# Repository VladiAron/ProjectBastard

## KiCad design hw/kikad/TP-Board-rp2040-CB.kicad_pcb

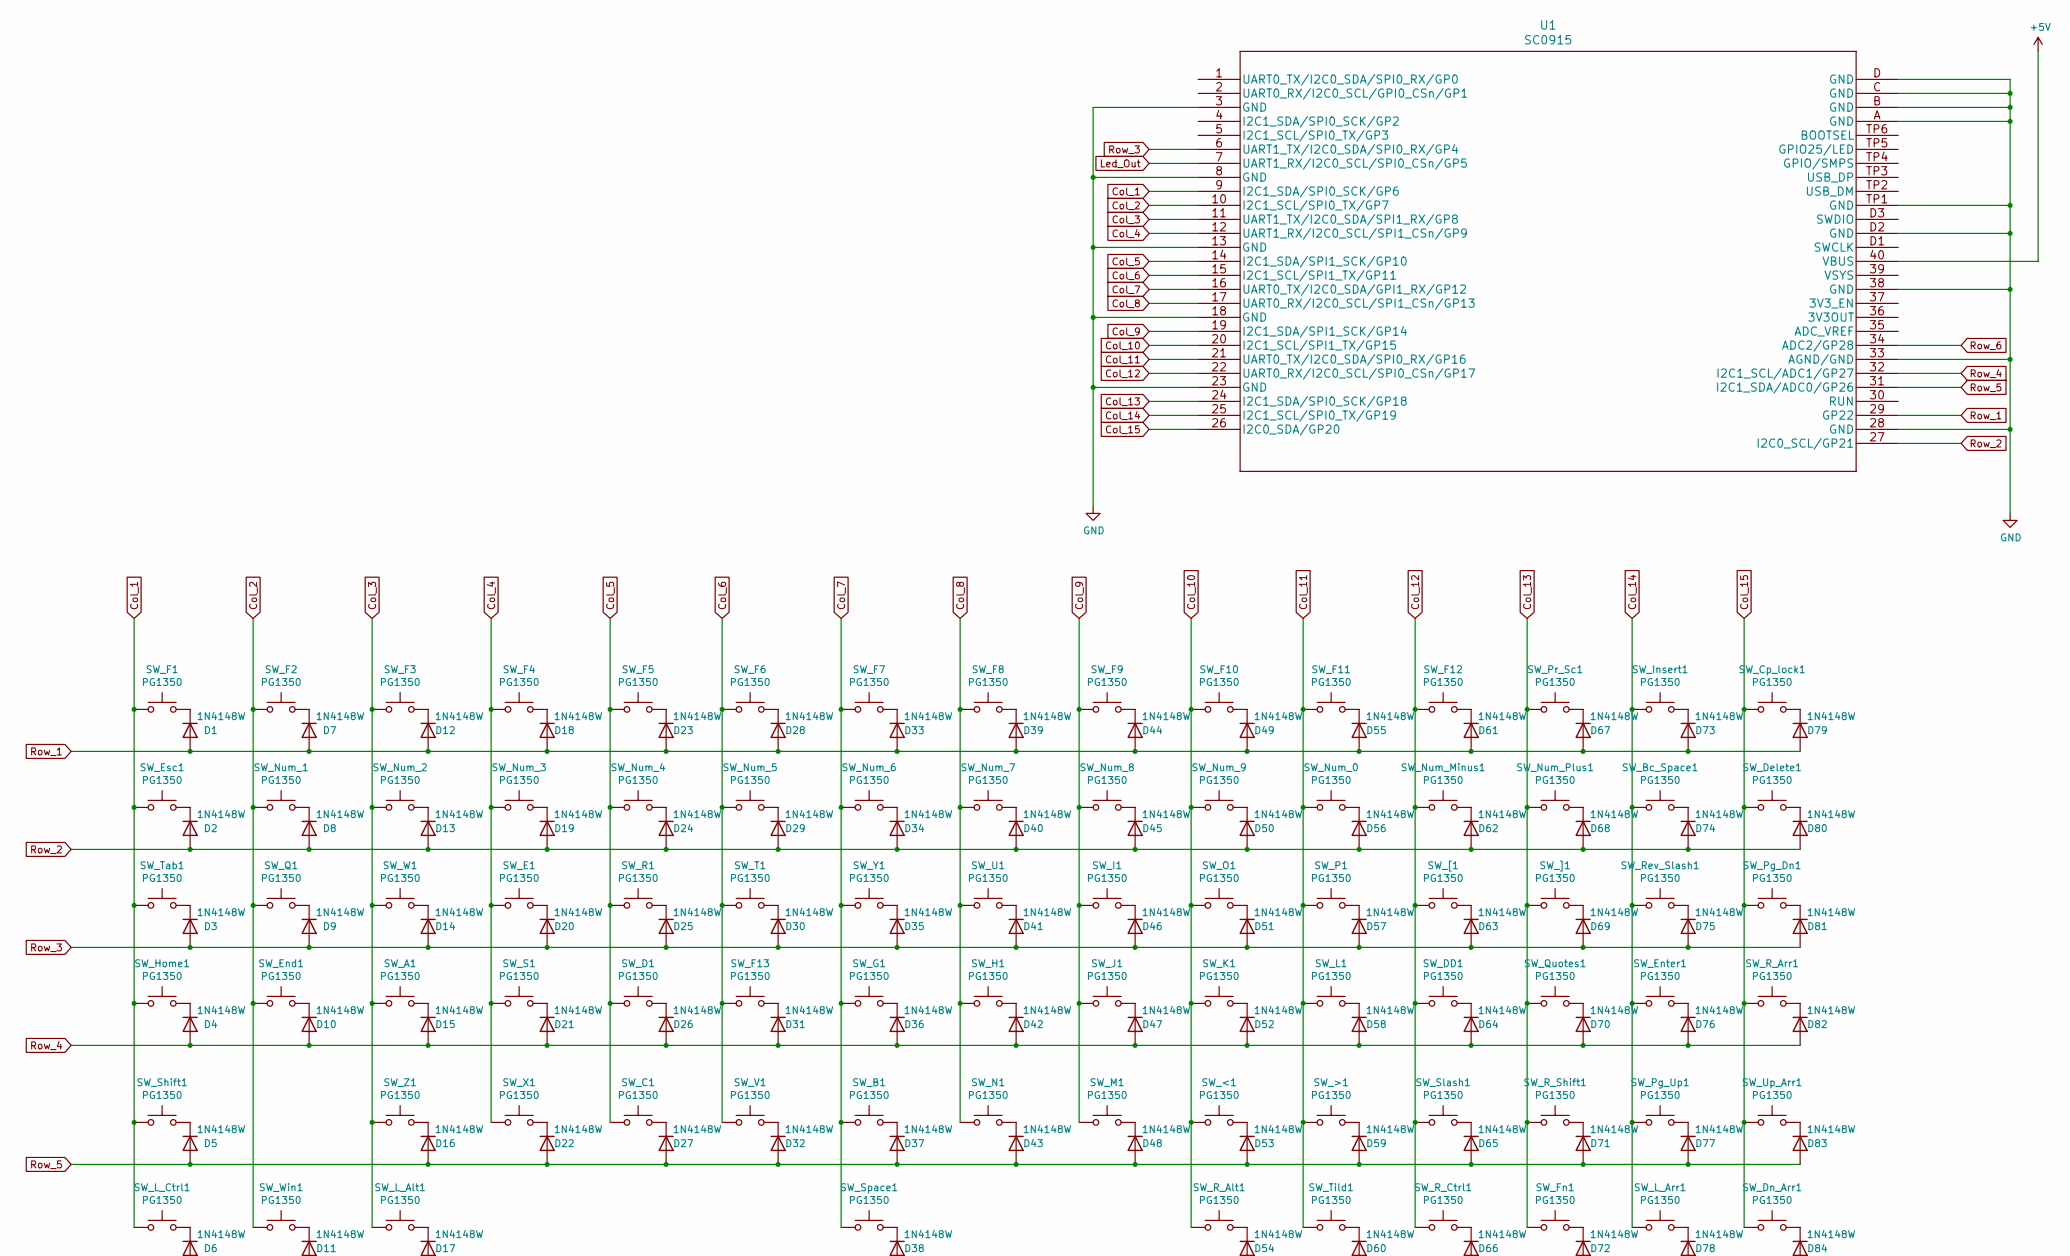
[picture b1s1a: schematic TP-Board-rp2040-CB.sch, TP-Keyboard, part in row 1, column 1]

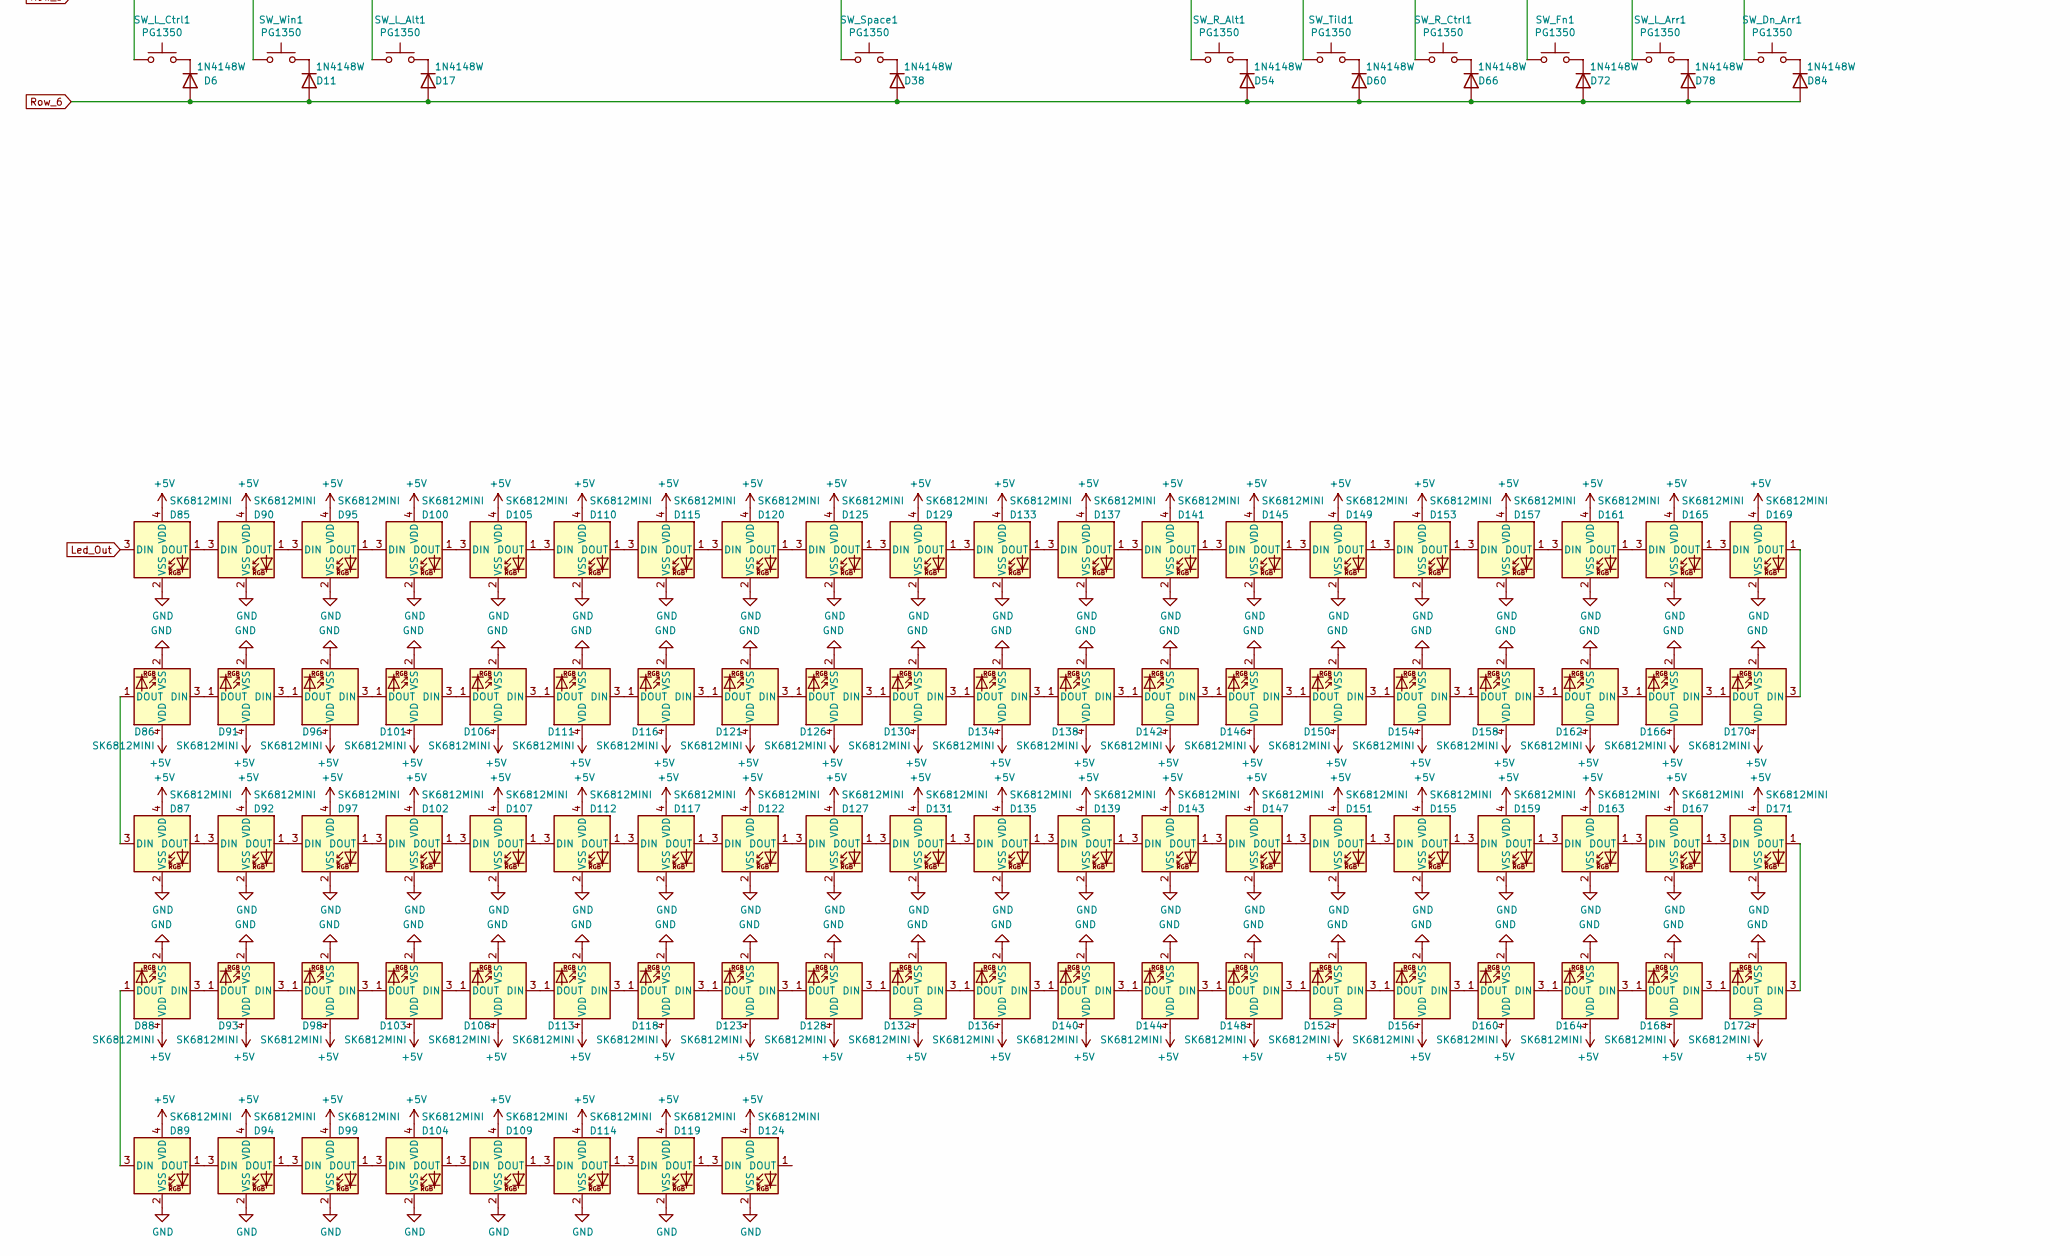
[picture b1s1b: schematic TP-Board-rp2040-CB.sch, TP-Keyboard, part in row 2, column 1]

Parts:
D1, D2, D3, D4, D5, D6, D7, D8, D9, D10, D11, D12, D13, D14, D15, D16, D17, D18, D19, D20, D21, D22, D23, D24, D25, D26, D27, D28, D29, D30, D31, D32, D33, D34, D35, D36, D37, D38, D39, D40, D41, D42, D43, D44, D45, D46, D47, D48, D49, D50, D51, D52, D53, D54, D55, D56, D57, D58, D59, D60, D61, D62, D63, D64, D65, D66, D67, D68, D69, D70, D71, D72, D73, D74, D75, D76, D77, D78, D79, D80, D81, D82, D83, D84: 1N4148W; D_SOD-123
D85, D86, D87, D88, D89, D90, D91, D92, D93, D94, D95, D96, D97, D98, D99, D100, D101, D102, D103, D104, D105, D106, D107, D108, D109, D110, D111, D112, D113, D114, D115, D116, D117, D118, D119, D120, D121, D122, D123, D124, D125, D126, D127, D128, D129, D130, D131, D132, D133, D134, D135, D136, D137, D138, D139, D140, D141, D142, D143, D144, D145, D146, D147, D148, D149, D150, D151, D152, D153, D154, D155, D156, D157, D158, D159, D160, D161, D162, D163, D164, D165, D166, D167, D168, D169, D170, D171, D172: SK6812MINI; LED_SK6812MINI_PLCC4_3.5x3.5mm_P1.75mm
SW_<1: PG1350; SW_PG1350
SW_>1: PG1350; SW_PG1350
SW_A1: PG1350; SW_PG1350
SW_B1: PG1350; SW_PG1350
SW_Bc_Space1: PG1350; SW_PG1350
SW_C1: PG1350; SW_PG1350
SW_Cp_lock1: PG1350; SW_PG1350
SW_D1: PG1350; SW_PG1350
SW_DD1: PG1350; SW_PG1350
SW_Delete1: PG1350; SW_PG1350
SW_Dn_Arr1: PG1350; SW_PG1350
SW_E1: PG1350; SW_PG1350
SW_End1: PG1350; SW_PG1350
SW_Enter1: PG1350; SW_PG1350
SW_Esc1: PG1350; SW_PG1350
SW_F1, SW_F2, SW_F3, SW_F4, SW_F5, SW_F6, SW_F7, SW_F8, SW_F9, SW_F10, SW_F11, SW_F12, SW_F13: PG1350; SW_PG1350
SW_Fn1: PG1350; SW_PG1350
SW_G1: PG1350; SW_PG1350
SW_H1: PG1350; SW_PG1350
SW_Home1: PG1350; SW_PG1350
SW_I1: PG1350; SW_PG1350
SW_Insert1: PG1350; SW_PG1350
SW_J1: PG1350; SW_PG1350
SW_K1: PG1350; SW_PG1350
SW_L1: PG1350; SW_PG1350
SW_L_Alt1: PG1350; SW_PG1350
SW_L_Arr1: PG1350; SW_PG1350
SW_L_Ctrl1: PG1350; SW_PG1350
SW_M1: PG1350; SW_PG1350
SW_N1: PG1350; SW_PG1350
SW_Num_0, SW_Num_1, SW_Num_2, SW_Num_3, SW_Num_4, SW_Num_5, SW_Num_6, SW_Num_7, SW_Num_8, SW_Num_9: PG1350; SW_PG1350
SW_Num_Minus1: PG1350; SW_PG1350
SW_Num_Plus1: PG1350; SW_PG1350
SW_O1: PG1350; SW_PG1350
SW_P1: PG1350; SW_PG1350
SW_Pg_Dn1: PG1350; SW_PG1350
SW_Pg_Up1: PG1350; SW_PG1350
SW_Pr_Sc1: PG1350; SW_PG1350
SW_Q1: PG1350; SW_PG1350
SW_Quotes1: PG1350; SW_PG1350
SW_R1: PG1350; SW_PG1350
SW_R_Alt1: PG1350; SW_PG1350
SW_R_Arr1: PG1350; SW_PG1350
SW_R_Ctrl1: PG1350; SW_PG1350
SW_R_Shift1: PG1350; SW_PG1350
SW_Rev_Slash1: PG1350; SW_PG1350
SW_S1: PG1350; SW_PG1350
SW_Shift1: PG1350; SW_PG1350
SW_Slash1: PG1350; SW_PG1350
SW_Space1: PG1350; SW_PG1350
SW_T1: PG1350; SW_PG1350
SW_Tab1: PG1350; SW_PG1350
SW_Tild1: PG1350; SW_PG1350
SW_U1: PG1350; SW_PG1350
SW_Up_Arr1: PG1350; SW_PG1350
SW_V1: PG1350; SW_PG1350
SW_W1: PG1350; SW_PG1350
SW_Win1: PG1350; SW_PG1350
SW_X1: PG1350; SW_PG1350
SW_Y1: PG1350; SW_PG1350
SW_Z1: PG1350; SW_PG1350
SW_[1: PG1350; SW_PG1350
SW_]1: PG1350; SW_PG1350
U1: SC0915; RPi_Pico_SMD_TH

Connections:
+5V: D85.4 (VDD), D86.4 (VDD), D87.4 (VDD), D88.4 (VDD), D89.4 (VDD), D90.4 (VDD), D91.4 (VDD), D92.4 (VDD), D93.4 (VDD), D94.4 (VDD), D95.4 (VDD), D96.4 (VDD), D97.4 (VDD), D98.4 (VDD), D99.4 (VDD), D100.4 (VDD), D101.4 (VDD), D102.4 (VDD), D103.4 (VDD), D104.4 (VDD), D105.4 (VDD), D106.4 (VDD), D107.4 (VDD), D108.4 (VDD), D109.4 (VDD), D110.4 (VDD), D111.4 (VDD), D112.4 (VDD), D113.4 (VDD), D114.4 (VDD), D115.4 (VDD), D116.4 (VDD), D117.4 (VDD), D118.4 (VDD), D119.4 (VDD), D120.4 (VDD), D121.4 (VDD), D122.4 (VDD), D123.4 (VDD), D124.4 (VDD), D125.4 (VDD), D126.4 (VDD), D127.4 (VDD), D128.4 (VDD), D129.4 (VDD), D130.4 (VDD), D131.4 (VDD), D132.4 (VDD), D133.4 (VDD), D134.4 (VDD), D135.4 (VDD), D136.4 (VDD), D137.4 (VDD), D138.4 (VDD), D139.4 (VDD), D140.4 (VDD), D141.4 (VDD), D142.4 (VDD), D143.4 (VDD), D144.4 (VDD), D145.4 (VDD), D146.4 (VDD), D147.4 (VDD), D148.4 (VDD), D149.4 (VDD), D150.4 (VDD), D151.4 (VDD), D152.4 (VDD), D153.4 (VDD), D154.4 (VDD), D155.4 (VDD), D156.4 (VDD), D157.4 (VDD), D158.4 (VDD), D159.4 (VDD), D160.4 (VDD), D161.4 (VDD), D162.4 (VDD), D163.4 (VDD), D164.4 (VDD), D165.4 (VDD), D166.4 (VDD), D167.4 (VDD), D168.4 (VDD), D169.4 (VDD), D170.4 (VDD), D171.4 (VDD), D172.4 (VDD), U1.40 (VBUS)
Col_1: SW_Esc1.1, SW_F1.1, SW_Home1.1, SW_L_Ctrl1.1, SW_Shift1.1, SW_Tab1.1, U1.9 (I2C1_SDA/SPI0_SCK/GP6)
Col_2: SW_End1.1, SW_F2.1, SW_Num_1.1, SW_Q1.1, SW_Win1.1, U1.10 (I2C1_SCL/SPI0_TX/GP7)
Col_3: SW_A1.1, SW_F3.1, SW_L_Alt1.1, SW_Num_2.1, SW_W1.1, SW_Z1.1, U1.11 (UART1_TX/I2C0_SDA/SPI1_RX/GP8)
Col_4: SW_E1.1, SW_F4.1, SW_Num_3.1, SW_S1.1, SW_X1.1, U1.12 (UART1_RX/I2C0_SCL/SPI1_CSn/GP9)
Col_5: SW_C1.1, SW_D1.1, SW_F5.1, SW_Num_4.1, SW_R1.1, U1.14 (I2C1_SDA/SPI1_SCK/GP10)
Col_6: SW_F6.1, SW_F13.1, SW_Num_5.1, SW_T1.1, SW_V1.1, U1.15 (I2C1_SCL/SPI1_TX/GP11)
Col_7: SW_B1.1, SW_F7.1, SW_G1.1, SW_Num_6.1, SW_Space1.1, SW_Y1.1, U1.16 (UART0_TX/I2C0_SDA/GPI1_RX/GP12)
Col_8: SW_F8.1, SW_H1.1, SW_N1.1, SW_Num_7.1, SW_U1.1, U1.17 (UART0_RX/I2C0_SCL/SPI1_CSn/GP13)
Col_9: SW_F9.1, SW_I1.1, SW_J1.1, SW_M1.1, SW_Num_8.1, U1.19 (I2C1_SDA/SPI1_SCK/GP14)
Col_10: SW_<1.1, SW_F10.1, SW_K1.1, SW_Num_9.1, SW_O1.1, SW_R_Alt1.1, U1.20 (I2C1_SCL/SPI1_TX/GP15)
Col_11: SW_>1.1, SW_F11.1, SW_L1.1, SW_Num_0.1, SW_P1.1, SW_Tild1.1, U1.21 (UART0_TX/I2C0_SDA/SPI0_RX/GP16)
Col_12: SW_DD1.1, SW_F12.1, SW_Num_Minus1.1, SW_R_Ctrl1.1, SW_Slash1.1, SW_[1.1, U1.22 (UART0_RX/I2C0_SCL/SPI0_CSn/GP17)
Col_13: SW_Fn1.1, SW_Num_Plus1.1, SW_Pr_Sc1.1, SW_Quotes1.1, SW_R_Shift1.1, SW_]1.1, U1.24 (I2C1_SDA/SPI0_SCK/GP18)
Col_14: SW_Bc_Space1.1, SW_Enter1.1, SW_Insert1.1, SW_L_Arr1.1, SW_Pg_Up1.1, SW_Rev_Slash1.1, U1.25 (I2C1_SCL/SPI0_TX/GP19)
Col_15: SW_Cp_lock1.1, SW_Delete1.1, SW_Dn_Arr1.1, SW_Pg_Dn1.1, SW_R_Arr1.1, SW_Up_Arr1.1, U1.26 (I2C0_SDA/GP20)
GND: D85.2 (VSS), D86.2 (VSS), D87.2 (VSS), D88.2 (VSS), D89.2 (VSS), D90.2 (VSS), D91.2 (VSS), D92.2 (VSS), D93.2 (VSS), D94.2 (VSS), D95.2 (VSS), D96.2 (VSS), D97.2 (VSS), D98.2 (VSS), D99.2 (VSS), D100.2 (VSS), D101.2 (VSS), D102.2 (VSS), D103.2 (VSS), D104.2 (VSS), D105.2 (VSS), D106.2 (VSS), D107.2 (VSS), D108.2 (VSS), D109.2 (VSS), D110.2 (VSS), D111.2 (VSS), D112.2 (VSS), D113.2 (VSS), D114.2 (VSS), D115.2 (VSS), D116.2 (VSS), D117.2 (VSS), D118.2 (VSS), D119.2 (VSS), D120.2 (VSS), D121.2 (VSS), D122.2 (VSS), D123.2 (VSS), D124.2 (VSS), D125.2 (VSS), D126.2 (VSS), D127.2 (VSS), D128.2 (VSS), D129.2 (VSS), D130.2 (VSS), D131.2 (VSS), D132.2 (VSS), D133.2 (VSS), D134.2 (VSS), D135.2 (VSS), D136.2 (VSS), D137.2 (VSS), D138.2 (VSS), D139.2 (VSS), D140.2 (VSS), D141.2 (VSS), D142.2 (VSS), D143.2 (VSS), D144.2 (VSS), D145.2 (VSS), D146.2 (VSS), D147.2 (VSS), D148.2 (VSS), D149.2 (VSS), D150.2 (VSS), D151.2 (VSS), D152.2 (VSS), D153.2 (VSS), D154.2 (VSS), D155.2 (VSS), D156.2 (VSS), D157.2 (VSS), D158.2 (VSS), D159.2 (VSS), D160.2 (VSS), D161.2 (VSS), D162.2 (VSS), D163.2 (VSS), D164.2 (VSS), D165.2 (VSS), D166.2 (VSS), D167.2 (VSS), D168.2 (VSS), D169.2 (VSS), D170.2 (VSS), D171.2 (VSS), D172.2 (VSS), U1.3 (GND), U1.8 (GND), U1.13 (GND), U1.18 (GND), U1.23 (GND), U1.28 (GND), U1.33 (AGND/GND), U1.38 (GND), U1.A (GND), U1.B (GND), U1.C (GND), U1.D (GND), U1.D2 (GND), U1.TP1 (GND)
Led_Out: D85.3 (DIN), U1.7 (UART1_RX/I2C0_SCL/SPI0_CSn/GP5)
unnamed: D1.1 (K), SW_F1.2
unnamed: D2.1 (K), SW_Esc1.2
unnamed: D3.1 (K), SW_Tab1.2
unnamed: D4.1 (K), SW_Home1.2
unnamed: D5.1 (K), SW_Shift1.2
unnamed: D6.1 (K), SW_L_Ctrl1.2
unnamed: D7.1 (K), SW_F2.2
unnamed: D8.1 (K), SW_Num_1.2
unnamed: D9.1 (K), SW_Q1.2
unnamed: D10.1 (K), SW_End1.2
unnamed: D11.1 (K), SW_Win1.2
unnamed: D12.1 (K), SW_F3.2
unnamed: D13.1 (K), SW_Num_2.2
unnamed: D14.1 (K), SW_W1.2
unnamed: D15.1 (K), SW_A1.2
unnamed: D16.1 (K), SW_Z1.2
unnamed: D17.1 (K), SW_L_Alt1.2
unnamed: D18.1 (K), SW_F4.2
unnamed: D19.1 (K), SW_Num_3.2
unnamed: D20.1 (K), SW_E1.2
unnamed: D21.1 (K), SW_S1.2
unnamed: D22.1 (K), SW_X1.2
unnamed: D23.1 (K), SW_F5.2
unnamed: D24.1 (K), SW_Num_4.2
unnamed: D25.1 (K), SW_R1.2
unnamed: D26.1 (K), SW_D1.2
unnamed: D27.1 (K), SW_C1.2
unnamed: D28.1 (K), SW_F6.2
unnamed: D29.1 (K), SW_Num_5.2
unnamed: D30.1 (K), SW_T1.2
unnamed: D31.1 (K), SW_F13.2
unnamed: D32.1 (K), SW_V1.2
unnamed: D33.1 (K), SW_F7.2
unnamed: D34.1 (K), SW_Num_6.2
unnamed: D35.1 (K), SW_Y1.2
unnamed: D36.1 (K), SW_G1.2
unnamed: D37.1 (K), SW_B1.2
unnamed: D38.1 (K), SW_Space1.2
unnamed: D39.1 (K), SW_F8.2
unnamed: D40.1 (K), SW_Num_7.2
unnamed: D41.1 (K), SW_U1.2
unnamed: D42.1 (K), SW_H1.2
unnamed: D43.1 (K), SW_N1.2
unnamed: D44.1 (K), SW_F9.2
unnamed: D45.1 (K), SW_Num_8.2
unnamed: D46.1 (K), SW_I1.2
unnamed: D47.1 (K), SW_J1.2
unnamed: D48.1 (K), SW_M1.2
unnamed: D49.1 (K), SW_F10.2
unnamed: D50.1 (K), SW_Num_9.2
unnamed: D51.1 (K), SW_O1.2
unnamed: D52.1 (K), SW_K1.2
unnamed: D53.1 (K), SW_<1.2
unnamed: D54.1 (K), SW_R_Alt1.2
unnamed: D55.1 (K), SW_F11.2
unnamed: D56.1 (K), SW_Num_0.2
unnamed: D57.1 (K), SW_P1.2
unnamed: D58.1 (K), SW_L1.2
unnamed: D59.1 (K), SW_>1.2
unnamed: D60.1 (K), SW_Tild1.2
unnamed: D61.1 (K), SW_F12.2
unnamed: D62.1 (K), SW_Num_Minus1.2
unnamed: D63.1 (K), SW_[1.2
unnamed: D64.1 (K), SW_DD1.2
unnamed: D65.1 (K), SW_Slash1.2
unnamed: D66.1 (K), SW_R_Ctrl1.2
unnamed: D67.1 (K), SW_Pr_Sc1.2
unnamed: D68.1 (K), SW_Num_Plus1.2
unnamed: D69.1 (K), SW_]1.2
unnamed: D70.1 (K), SW_Quotes1.2
unnamed: D71.1 (K), SW_R_Shift1.2
unnamed: D72.1 (K), SW_Fn1.2
unnamed: D73.1 (K), SW_Insert1.2
unnamed: D74.1 (K), SW_Bc_Space1.2
unnamed: D75.1 (K), SW_Rev_Slash1.2
unnamed: D76.1 (K), SW_Enter1.2
unnamed: D77.1 (K), SW_Pg_Up1.2
unnamed: D78.1 (K), SW_L_Arr1.2
unnamed: D79.1 (K), SW_Cp_lock1.2
unnamed: D80.1 (K), SW_Delete1.2
unnamed: D81.1 (K), SW_Pg_Dn1.2
unnamed: D82.1 (K), SW_R_Arr1.2
unnamed: D83.1 (K), SW_Up_Arr1.2
unnamed: D84.1 (K), SW_Dn_Arr1.2
unnamed: D85.1 (DOUT), D90.3 (DIN)
unnamed: D86.1 (DOUT), D87.3 (DIN)
unnamed: D86.3 (DIN), D91.1 (DOUT)
unnamed: D87.1 (DOUT), D92.3 (DIN)
unnamed: D88.1 (DOUT), D89.3 (DIN)
unnamed: D88.3 (DIN), D93.1 (DOUT)
unnamed: D89.1 (DOUT), D94.3 (DIN)
unnamed: D90.1 (DOUT), D95.3 (DIN)
unnamed: D91.3 (DIN), D96.1 (DOUT)
unnamed: D92.1 (DOUT), D97.3 (DIN)
unnamed: D93.3 (DIN), D98.1 (DOUT)
unnamed: D94.1 (DOUT), D99.3 (DIN)
unnamed: D100.1 (DOUT), D105.3 (DIN)
unnamed: D95.1 (DOUT), D100.3 (DIN)
unnamed: D96.3 (DIN), D101.1 (DOUT)
unnamed: D101.3 (DIN), D106.1 (DOUT)
unnamed: D102.1 (DOUT), D107.3 (DIN)
unnamed: D97.1 (DOUT), D102.3 (DIN)
unnamed: D98.3 (DIN), D103.1 (DOUT)
unnamed: D103.3 (DIN), D108.1 (DOUT)
unnamed: D104.1 (DOUT), D109.3 (DIN)
unnamed: D99.1 (DOUT), D104.3 (DIN)
unnamed: D105.1 (DOUT), D110.3 (DIN)
unnamed: D106.3 (DIN), D111.1 (DOUT)
unnamed: D107.1 (DOUT), D112.3 (DIN)
unnamed: D108.3 (DIN), D113.1 (DOUT)
unnamed: D109.1 (DOUT), D114.3 (DIN)
unnamed: D110.1 (DOUT), D115.3 (DIN)
unnamed: D111.3 (DIN), D116.1 (DOUT)
unnamed: D112.1 (DOUT), D117.3 (DIN)
unnamed: D113.3 (DIN), D118.1 (DOUT)
unnamed: D114.1 (DOUT), D119.3 (DIN)
unnamed: D115.1 (DOUT), D120.3 (DIN)
unnamed: D116.3 (DIN), D121.1 (DOUT)
unnamed: D117.1 (DOUT), D122.3 (DIN)
unnamed: D118.3 (DIN), D123.1 (DOUT)
unnamed: D119.1 (DOUT), D124.3 (DIN)
unnamed: D120.1 (DOUT), D125.3 (DIN)
unnamed: D121.3 (DIN), D126.1 (DOUT)
unnamed: D122.1 (DOUT), D127.3 (DIN)
unnamed: D123.3 (DIN), D128.1 (DOUT)
unnamed: D125.1 (DOUT), D129.3 (DIN)
unnamed: D126.3 (DIN), D130.1 (DOUT)
unnamed: D127.1 (DOUT), D131.3 (DIN)
unnamed: D128.3 (DIN), D132.1 (DOUT)
unnamed: D129.1 (DOUT), D133.3 (DIN)
unnamed: D130.3 (DIN), D134.1 (DOUT)
unnamed: D131.1 (DOUT), D135.3 (DIN)
unnamed: D132.3 (DIN), D136.1 (DOUT)
unnamed: D133.1 (DOUT), D137.3 (DIN)
unnamed: D134.3 (DIN), D138.1 (DOUT)
unnamed: D135.1 (DOUT), D139.3 (DIN)
unnamed: D136.3 (DIN), D140.1 (DOUT)
unnamed: D137.1 (DOUT), D141.3 (DIN)
unnamed: D138.3 (DIN), D142.1 (DOUT)
unnamed: D139.1 (DOUT), D143.3 (DIN)
unnamed: D140.3 (DIN), D144.1 (DOUT)
unnamed: D141.1 (DOUT), D145.3 (DIN)
unnamed: D142.3 (DIN), D146.1 (DOUT)
unnamed: D143.1 (DOUT), D147.3 (DIN)
unnamed: D144.3 (DIN), D148.1 (DOUT)
unnamed: D145.1 (DOUT), D149.3 (DIN)
unnamed: D146.3 (DIN), D150.1 (DOUT)
unnamed: D147.1 (DOUT), D151.3 (DIN)
unnamed: D148.3 (DIN), D152.1 (DOUT)
unnamed: D149.1 (DOUT), D153.3 (DIN)
unnamed: D150.3 (DIN), D154.1 (DOUT)
unnamed: D151.1 (DOUT), D155.3 (DIN)
unnamed: D152.3 (DIN), D156.1 (DOUT)
unnamed: D153.1 (DOUT), D157.3 (DIN)
unnamed: D154.3 (DIN), D158.1 (DOUT)
unnamed: D155.1 (DOUT), D159.3 (DIN)
unnamed: D156.3 (DIN), D160.1 (DOUT)
unnamed: D157.1 (DOUT), D161.3 (DIN)
unnamed: D158.3 (DIN), D162.1 (DOUT)
unnamed: D159.1 (DOUT), D163.3 (DIN)
unnamed: D160.3 (DIN), D164.1 (DOUT)
unnamed: D161.1 (DOUT), D165.3 (DIN)
unnamed: D162.3 (DIN), D166.1 (DOUT)
unnamed: D163.1 (DOUT), D167.3 (DIN)
unnamed: D164.3 (DIN), D168.1 (DOUT)
unnamed: D165.1 (DOUT), D169.3 (DIN)
unnamed: D166.3 (DIN), D170.1 (DOUT)
unnamed: D167.1 (DOUT), D171.3 (DIN)
unnamed: D168.3 (DIN), D172.1 (DOUT)
unnamed: D169.1 (DOUT), D170.3 (DIN)
unnamed: D171.1 (DOUT), D172.3 (DIN)
Row_1: D1.2 (A), D7.2 (A), D12.2 (A), D18.2 (A), D23.2 (A), D28.2 (A), D33.2 (A), D39.2 (A), D44.2 (A), D49.2 (A), D55.2 (A), D61.2 (A), D67.2 (A), D73.2 (A), D79.2 (A), U1.29 (GP22)
Row_2: D2.2 (A), D8.2 (A), D13.2 (A), D19.2 (A), D24.2 (A), D29.2 (A), D34.2 (A), D40.2 (A), D45.2 (A), D50.2 (A), D56.2 (A), D62.2 (A), D68.2 (A), D74.2 (A), D80.2 (A), U1.27 (I2C0_SCL/GP21)
Row_3: D3.2 (A), D9.2 (A), D14.2 (A), D20.2 (A), D25.2 (A), D30.2 (A), D35.2 (A), D41.2 (A), D46.2 (A), D51.2 (A), D57.2 (A), D63.2 (A), D69.2 (A), D75.2 (A), D81.2 (A), U1.6 (UART1_TX/I2C0_SDA/SPI0_RX/GP4)
Row_4: D4.2 (A), D10.2 (A), D15.2 (A), D21.2 (A), D26.2 (A), D31.2 (A), D36.2 (A), D42.2 (A), D47.2 (A), D52.2 (A), D58.2 (A), D64.2 (A), D70.2 (A), D76.2 (A), D82.2 (A), U1.32 (I2C1_SCL/ADC1/GP27)
Row_5: D5.2 (A), D16.2 (A), D22.2 (A), D27.2 (A), D32.2 (A), D37.2 (A), D43.2 (A), D48.2 (A), D53.2 (A), D59.2 (A), D65.2 (A), D71.2 (A), D77.2 (A), D83.2 (A), U1.31 (I2C1_SDA/ADC0/GP26)
Row_6: D6.2 (A), D11.2 (A), D17.2 (A), D38.2 (A), D54.2 (A), D60.2 (A), D66.2 (A), D72.2 (A), D78.2 (A), D84.2 (A), U1.34 (ADC2/GP28)

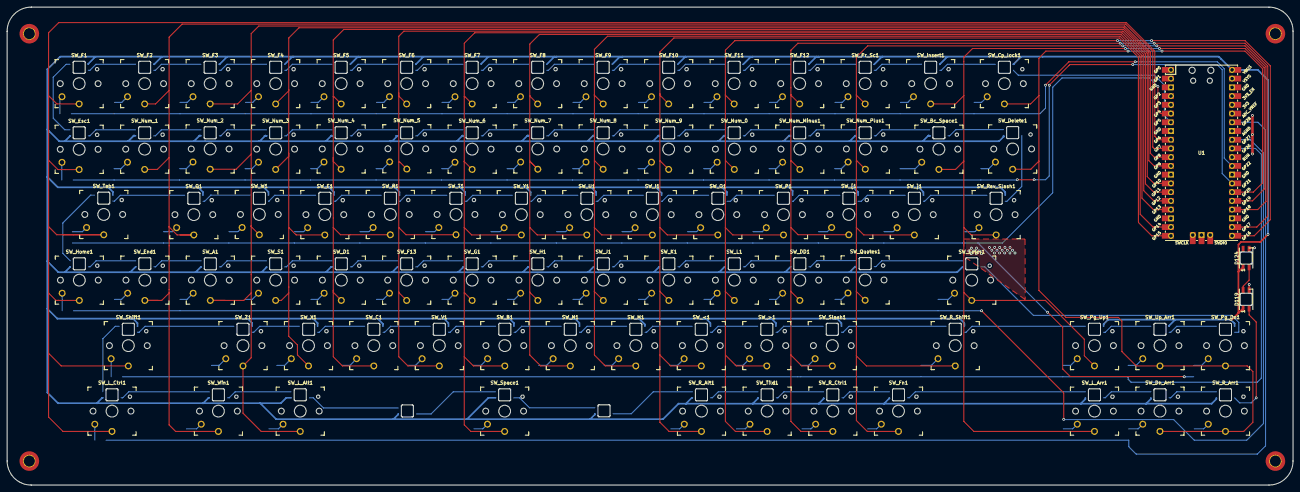
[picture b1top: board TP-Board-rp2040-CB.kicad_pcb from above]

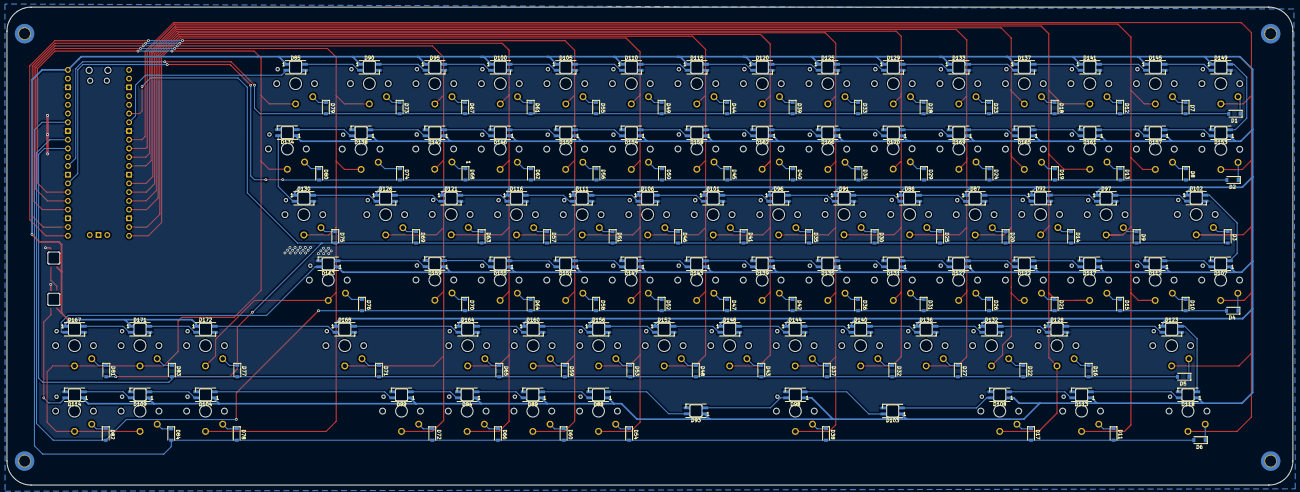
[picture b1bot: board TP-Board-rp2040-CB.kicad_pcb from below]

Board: 2 copper layers, 374.0 x 139.0 mm, 257 parts (170 on the bottom side), 195 nets.

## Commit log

2022-11-16 First kicad prj
